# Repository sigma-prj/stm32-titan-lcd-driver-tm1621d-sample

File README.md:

STM32 F030R8 NUCLEO Board Sample Application - How to drive LCD using Titan TM1621D driver
==============

This project represents sample STM32 F030R8 NUCLEO board application,
showing how to drive 7-Segments LCD using Titan TM1621D driver

The following methods are implemented within main application's source code:
 - ***submit_bits_array*** - data transfer to TM1621D LCD driver using pre-defined output PINs
 - ***submit_cmd*** - command submission to TM1621D LCD driver
 - ***submit_data*** - data submission to TM1621D LCD driver
 - ***put_matrix_symbol*** - specific symbol placement into matrix buffer
 - ***display_ methods*** - ability to display specific symbols on LCD

Requirements and Dependencies
-----------------------------

This application is targeted to be built and executed using STM32 CubeIDE.
New CubeIDE project needs to be created and configured as F030R8 NUCLEO board app.
Corresponding pins needs to be setup in .ioc file using CubeMX application.
Besides F030R8 NUCLEO pins set by default, the following should be configured:
 - ***PA8*** - GPIO Output (will be used as TM1621D Write signal)
 - ***PA15*** - GPIO Output (will be used as TM1621D Data signal)
 - ***PA11*** - GPIO Output (will be used as TM1621D CS signal)

Once the project is created, the main file at Core/Src/ subfolder can be substituted by
main.c file from repo.

KiCad Design Files
-----------------------------

In order to run this application with specified Titan LCD Driver
and presented LCD chip - special adapter PCB can be used (pluggable into STM32 F030R8 NUCLEO board)
KiCad schema and PCB layout design files can be found under 'kicad' subfolder.

More Details
-----------------------------

More information can be found at corresponding YouTube video:
https://www.youtube.com/watch?v=M4Ayx5ZT4EI

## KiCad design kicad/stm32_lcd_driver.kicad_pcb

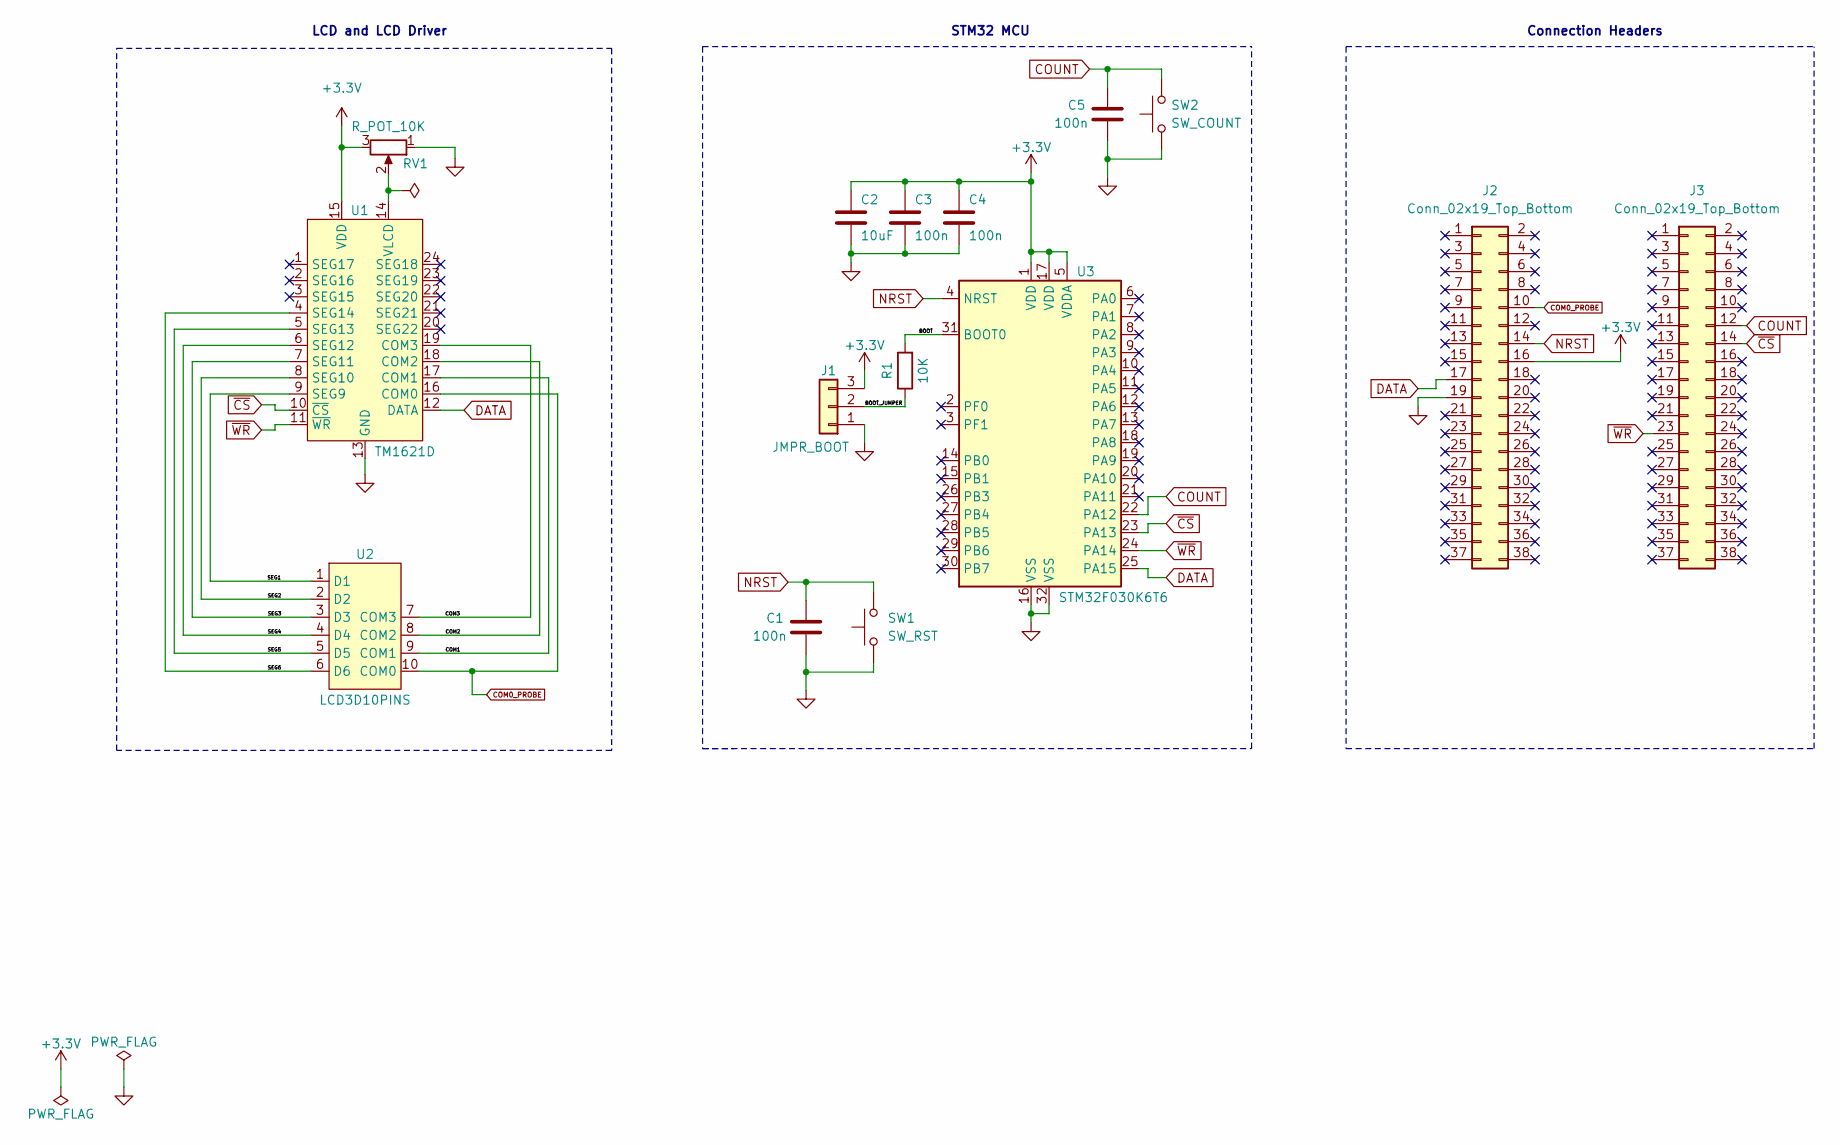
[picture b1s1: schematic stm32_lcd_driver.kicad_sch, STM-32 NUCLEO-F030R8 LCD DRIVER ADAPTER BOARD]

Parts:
C1, C3, C4, C5: 100n; C_0603_1608Metric_Pad1.08x0.95mm_HandSolder
C2: 10uF; C_0603_1608Metric_Pad1.08x0.95mm_HandSolder
J1: JMPR_BOOT; PinHeader_1x03_P2.54mm_Vertical
J2, J3: Conn_02x19_Top_Bottom; PinHeader_2x19_P2.54mm_Vertical
R1: 10K; R_0603_1608Metric_Pad0.98x0.95mm_HandSolder
RV1: R_POT_10K; Potentiometer_Bourns_3296W_Vertical
SW1: SW_RST; SW_PUSH_V2-12mm
SW2: SW_COUNT; SW_PUSH_V2-12mm
U1: TM1621D; SOP-24_7.5x15.4mm_P1.27mm
U2: LCD3D10PINS
U3: STM32F030K6T6; LQFP-32_7x7mm_P0.8mm

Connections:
+3.3V: C2.1, C3.1, C4.1, J1.3, J2.16, RV1.3, U1.15 (VDD), U3.1 (VDD), U3.5 (VDDA), U3.17 (VDD)
/BOOT: R1.2, U3.31 (BOOT0)
/BOOT_JUMPER: J1.2, R1.1
/COM1: U1.17 (COM1), U2.9 (COM1)
/COM2: U1.18 (COM2), U2.8 (COM2)
/COM3: U1.19 (COM3), U2.7 (COM3)
/SEG1: U1.9 (SEG9), U2.1 (D1)
/SEG2: U1.8 (SEG10), U2.2 (D2)
/SEG3: U1.7 (SEG11), U2.3 (D3)
/SEG4: U1.6 (SEG12), U2.4 (D4)
/SEG5: U1.5 (SEG13), U2.5 (D5)
/SEG6: U1.4 (SEG14), U2.6 (D6)
COM0_PROBE: J2.10, U1.16 (COM0), U2.10 (COM0)
COUNT: C5.1, J3.12, SW2.2, U3.22 (PA12)
DATA: J2.17, U1.12 (DATA), U3.25 (PA15)
GND: C1.2, C2.2, C3.2, C4.2, C5.2, J1.1, J2.19, RV1.1, SW1.1, SW2.1, U1.13 (GND), U3.16 (VSS), U3.32 (VSS)
NRST: C1.1, J2.14, SW1.2, U3.4 (NRST)
unnamed: RV1.2, U1.14 (VLCD)
~CS: J3.14, U1.10 (~CS), U3.23 (PA13)
~WR: J3.23, U1.11 (~WR), U3.24 (PA14)

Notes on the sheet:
LCD and LCD Driver
STM32 MCU
Connection Headers

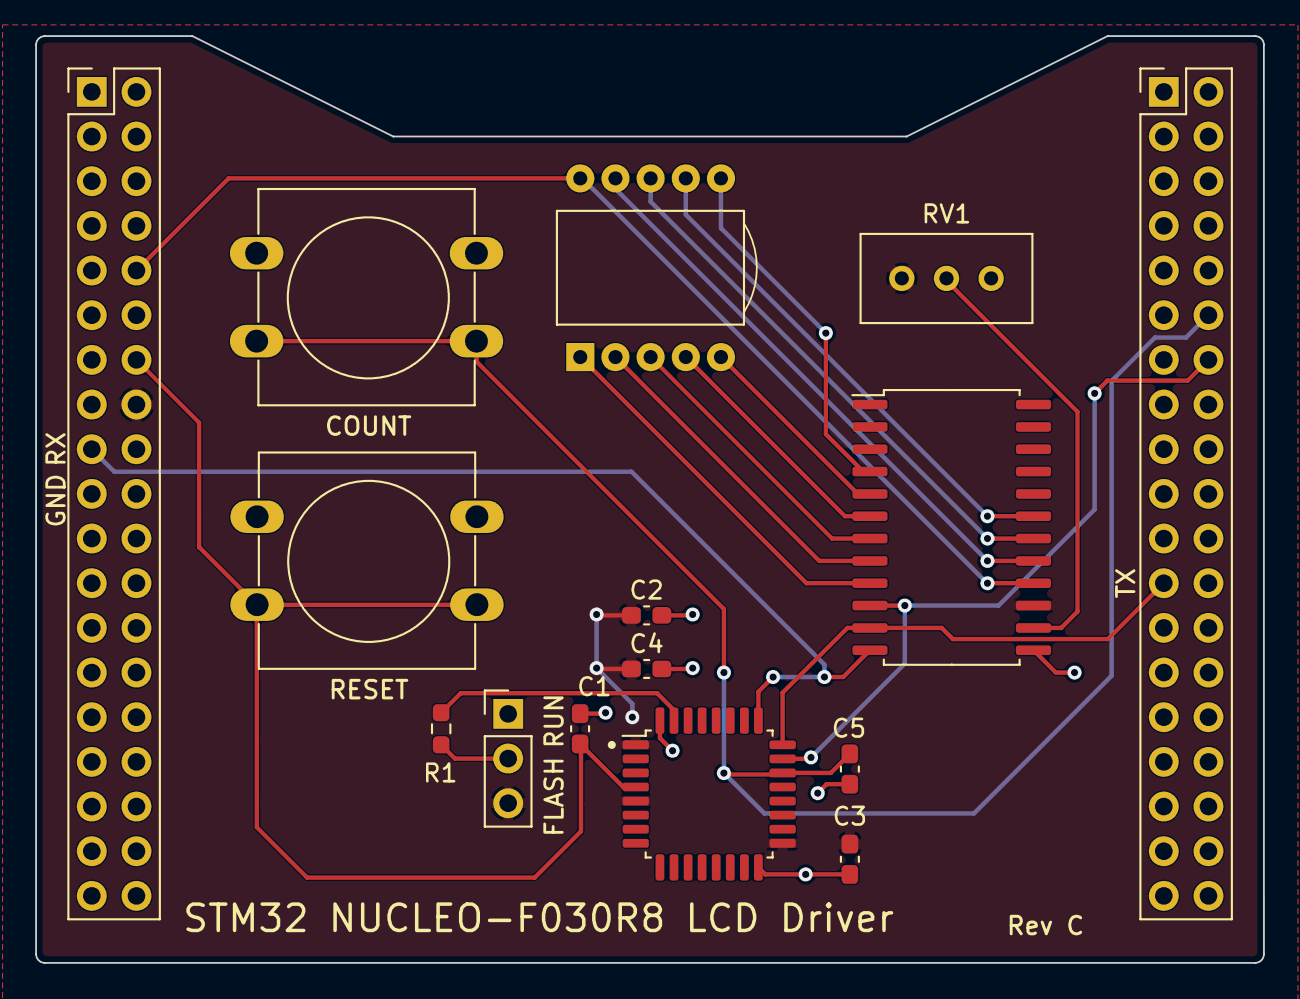
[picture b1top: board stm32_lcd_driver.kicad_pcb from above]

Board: 2 copper layers, 69.8 x 52.7 mm, 15 parts (0 on the bottom side), 20 nets.

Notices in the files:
kicad/stm32_lcd_driver.kicad_pcb:
https://creativecommons.org/licenses/by/4.0
License: Attribution 4.0 International (CC BY 4.0)
